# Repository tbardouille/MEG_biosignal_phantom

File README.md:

# An open source phantom for MEG

## Consistent measurement of localization error across sites

### Motivation

Magnetoencephalography (MEG) is used to localize sources of neuronal activity, where the current dipole is the fundamental model used to estimate the sources in the brain. There is no ground truth for the accuracy and precision of localization of such sources within the brain, so it is imperative to have an independent quantification of an MEG system’s source localization accuracy. Localization error can be assessed with a phantom - a device that contains small current elements (wire segments) with known position and orientation. The wire segments can be localized based on MEG data capturing their activation (using a current dipole model). This provides a useful estimate of uncertainty in MEG results and a platform to compare performance based on hardware or software innovations. 

We have developed a simple dry phantom. Here, we share the build instructions and validation results, to provide a common platform for measuring MEG system performance. 

## Relating Phantom Design to Human MEG Scans

The phantom has two types of sources:  short, straight wire segments (modelled as current dipoles) to simulate brain activity and small wire loops (modelled as magnetic dipoles) to simulate head tracking. The small loops are equivalent to the head position indicator (HPI) coils, which are activated to estimate the position and orientation of the head (or phantom) within the helmet coordinate frame. The localization of our four HPI coils defines the transformation between helmet and phantom coordinate frames. We have designed a dry phantom that uses four narrow isosceles triangles of wire, where the short edge of the triangle is the wire segment that simulates brain activity. The wire segments generate magnetic field changes that are equivalent to brain activity. The MEG data can be used to estimate the position and orientation of simulated brain activity in the helmet coordinate frame. These locations are transformed to give the wire segment position and orientation in the phantom coordinate frame, and these transformed values are compared to the expected values.  This use case of the phantom mimics head tracking and source localization in MEG, so that phantom quantification of localization accuracy can be transferred to human recordings.

## What is in this repository?

* <b>README.md</b> - this file
* <b>phantomVersion1</b> - folder containing the first version of the PCB phantom
	+ Build Instructions.md - markdown instructions for building the phantom
	+ phantom-Platform.stl - a 3D printable file containing the phantom platform
	+ gerbers - a folder containing files necessary to print the printed circuit board (PCB)
	+ phantomDrive_V4.ino - Arduino code to run the current driver (i.e., activate sources)
	+ Circuit Layout.png - a circuit diagram for the current driver 
	+ designFiles - a folder containing FreeCAD and KiCAD design files
	+ if you edit the design, please share this back to the repo (<b>under Contributors</b>)
* <b>pictures</b> - a folder including pictures used in markdown files
* <b>Results</b> - markdown files describing findings with various phantom builds
* <b>Contributors</b> - a folder for contriibuting sites to keep their development files

## Validation Results

Validation data was acquired at the Biosignal Lab at Dalhousie University (Halifax, NS, Canada). We used 16 Fieldline v2 single-axis OPM sensors inside of a 2-layre mu-metal shielded cylinder. The sensor helmet had 107 slots - we made consecutive recordings of the phantom with sensors in different slots to capture whole-head MEG data.  The phantom was mounted directly onto the helmet using 3D printed mounting pieces to attach it to 3 of the sensor slots - enabling consistent phantom platform position across recordings. One whole-head recording was the compilation of eight acquisition runs with sensors in different helmet slots each time to cover 94 total sensor positions (after lost data). Data was recorded at 1000 Hz. The current driver was set to provide 17 nAm. Dipole locations are all 6.50 cm from the origin. Polar angles are -60, -15, 25, and 70 degrees. 

Below, we show representative field topographies for the HPI coils (top row) and wire segments (bottom row), averaged over 100 epochs and centered at the peak of the pulses that were delivered. 

HPI and ECDs were localized. HPI data were used to establish the phantom to MEG coordinate frame transformation. ECDs were localized in the MEG coordinate frame and positions were transformed to the phantom coordinate frame (i.e., absolute localization error). The table below shows difference between the estimated and known position across all ECDs, in Cartesian and spherical coordinate frames. As well, the straight-line localization error is shown. 

Our phantom acheives 2.2 +/- 1.1 mm localization error, with no evidence of systematic error (i.e., bias) in any dimension.

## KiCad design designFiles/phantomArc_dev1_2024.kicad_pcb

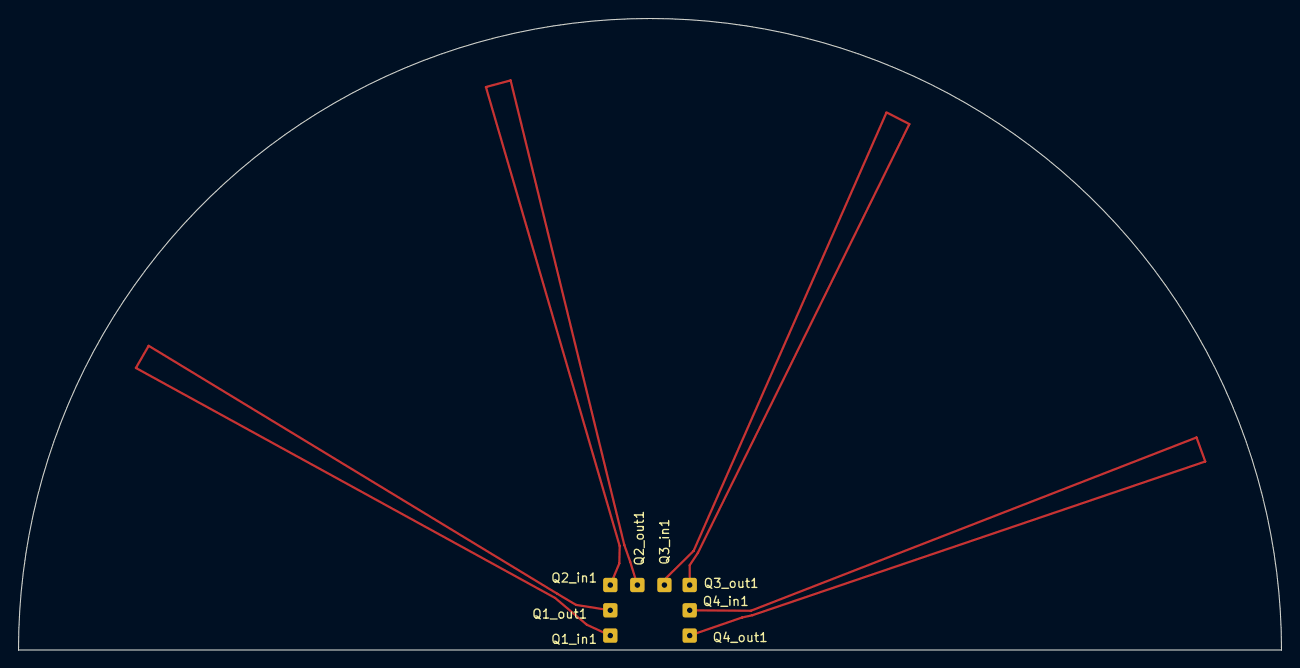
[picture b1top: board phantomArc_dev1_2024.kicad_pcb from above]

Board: 2 copper layers, 140.0 x 70.0 mm, 8 parts (0 on the bottom side), 4 nets.

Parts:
Q1_in1, Q1_out1, Q2_in1, Q2_out1, Q3_in1, Q3_out1, Q4_in1, Q4_out1: Conn_01x01_Pin; SolderWire-0.1sqmm_1x01_D0.4mm_OD1mm

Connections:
unnamed: Q1_in1.1, Q1_out1.1
unnamed: Q2_in1.1, Q2_out1.1
unnamed: Q3_in1.1, Q3_out1.1
unnamed: Q4_in1.1, Q4_out1.1

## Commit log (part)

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2025-09-22 Platform for PCB and HPI mounting
2025-09-22 PCB print files
2025-09-22 Arduino driver file
2025-09-22 Driver circuit
2025-09-22 Removed incorect gerbers
2025-09-22 Added correct gerbers
2025-09-22 Update README.md to include dipole positions
2025-09-22 Update README.md (formatting)
2025-09-30 Current driver file for Arduino added
2025-10-09 Added design files for PCB and platform
2025-10-09 Added markdown build instructions
2025-10-09 Smaller image files
2025-10-10 README updated to include project description and validation data
2026-02-16 Wrong PCB files
    Removing incorrect PCB files. The incorrect ones used a via for the ECD. Instead, we have the correct version, with a small tangential wire segment on one side.
2026-03-03 First draft
2026-03-04 Udpate
2026-03-04 Update2
2026-03-05 Update3
2026-03-05 Typo_fix
2026-03-05 Update_references_figs4-5
2026-03-05 Figure_equations_update
2026-03-05 Re-update
2026-03-05 Re-update2
2026-03-05 Test
2026-03-05 test3
2026-03-05 Quick_cleanup
2026-03-05 Test4
2026-03-10 Equations_as_figs
2026-03-10 Table_Factor_additions_Major_pathing_refactor
2026-03-10 Minorfix
2026-03-10 Updates_TBCK_reviews
2026-03-10 Slight_fix
2026-03-17 Fixes_v4
2026-03-17 small_fix
2026-03-19 Edits by suggestion of CK. Grammar fixes
2026-03-19 Small fixes
2026-03-31 TB Edits - Equation + moderate language changes
2026-04-10 Folders for each contributor
    Setting up a folder structure so that each contributing site has their own space
2026-04-14 Contributor folders initally populated
2026-04-14 README files added
2026-04-14 Add files via upload
    Fusion archive of phantom brain assembly
2026-04-14 Add files via upload
    Exported .step files of 3D printable phantom brain parts
2026-04-14 Add files via upload
    Quarter PCB tolerance tester
2026-04-14 renamed Nijmegen (with typo) to Donders, added first designs
2026-04-14 add image with first signal, fixed heading levels
2026-04-14 fiixed typo in gerbers directory
2026-04-26 added parts list at digikey

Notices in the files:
designFiles/phantomArc_dev1_2024.kicad_pcb:
creativecommons.org/license/by/4.0
License: CC BY 4.0
